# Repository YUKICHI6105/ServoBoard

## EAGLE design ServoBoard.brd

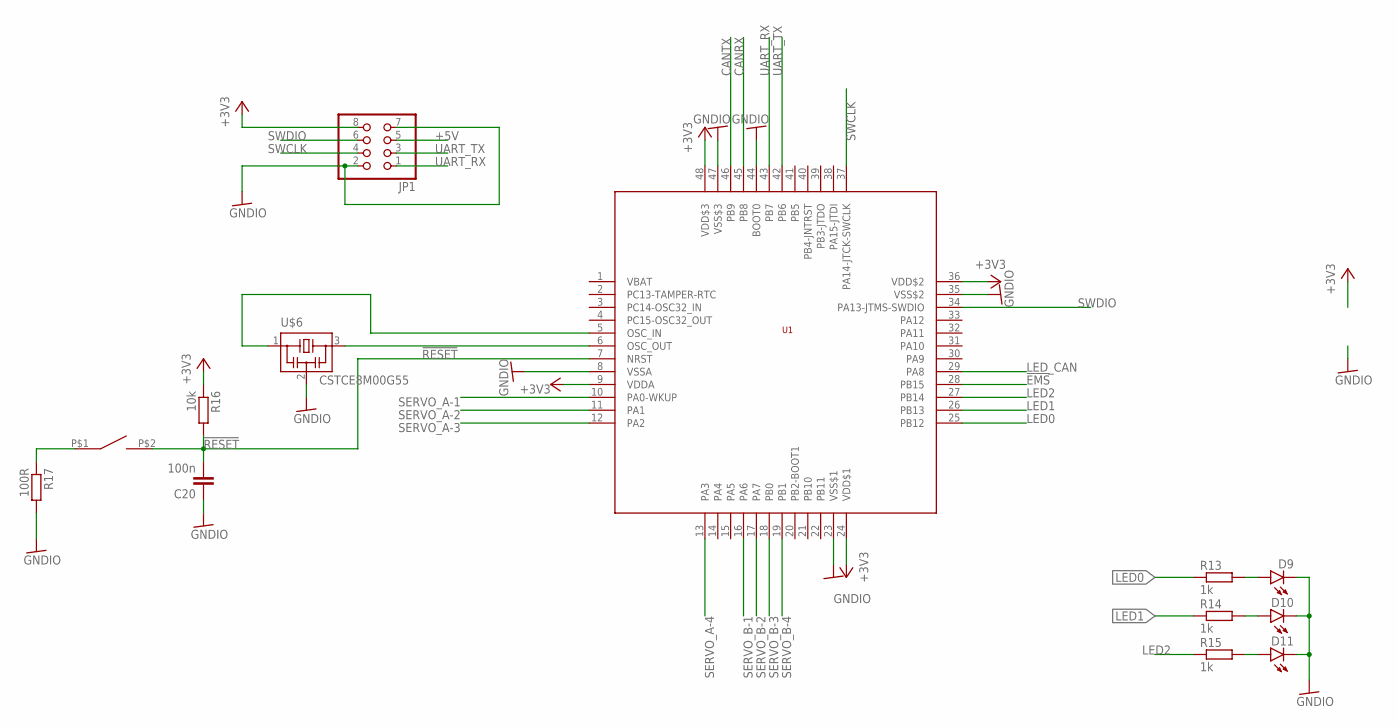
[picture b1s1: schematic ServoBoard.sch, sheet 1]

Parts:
C20: 100n; C0603
D9, D10, D11: LEDCHIPLED_0805; CHIPLED_0805
JP1: PINHD-2X4; 2X04
R13, R14, R15: 1k; R0603
R16: 10k; R0603
R17: 100R; R0603
SW1: SWITCH_TACTILETOP; SWITCH_TACTILE_3X6
U1: STM32F103C8; LQFP48
U$6: CSTCE8M00G55

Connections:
!EMS: U1.28 (PB15); also elsewhere on the board
!RESET: C20.2, R16.2, SW1.P$2 (2), U1.7 (NRST)
+3V3: JP1.8, R16.1, U1.9 (VDDA), U1.24 (VDD$1), U1.36 (VDD$2), U1.48 (VDD$3); also elsewhere on the board
+5V: JP1.5; also elsewhere on the board
CANRX: U1.45 (PB8); also elsewhere on the board
CANTX: U1.46 (PB9); also elsewhere on the board
GNDIO: C20.1, D9.C, D10.C, D11.C, JP1.2, JP1.7, R17.2, U1.8 (VSSA), U1.23 (VSS$1), U1.35 (VSS$2), U1.44 (BOOT0), U1.47 (VSS$3), U$6.2; also elsewhere on the board
LED0: R13.1, U1.25 (PB12)
LED1: R14.1, U1.26 (PB13)
LED2: R15.1, U1.27 (PB14)
LED_CAN: U1.29 (PA8); also elsewhere on the board
unnamed: D10.A, R14.2
unnamed: D9.A, R13.2
unnamed: U1.6 (OSC_OUT), U$6.3
unnamed: R17.1, SW1.P$1 (1)
unnamed: U1.5 (OSC_IN), U$6.1
unnamed: D11.A, R15.2
SERVO_A-1: U1.10 (PA0-WKUP); also elsewhere on the board
SERVO_A-2: U1.11 (PA1); also elsewhere on the board
SERVO_A-3: U1.12 (PA2); also elsewhere on the board
SERVO_A-4: U1.13 (PA3); also elsewhere on the board
SERVO_B-1: U1.16 (PA6); also elsewhere on the board
SERVO_B-2: U1.17 (PA7); also elsewhere on the board
SERVO_B-3: U1.18 (PB0); also elsewhere on the board
SERVO_B-4: U1.19 (PB1); also elsewhere on the board
SWCLK: JP1.4, U1.37 (PA14-JTCK-SWCLK)
SWDIO: JP1.6, U1.34 (PA13-JTMS-SWDIO)
UART_RX: JP1.1, U1.43 (PB7)
UART_TX: JP1.3, U1.42 (PB6)

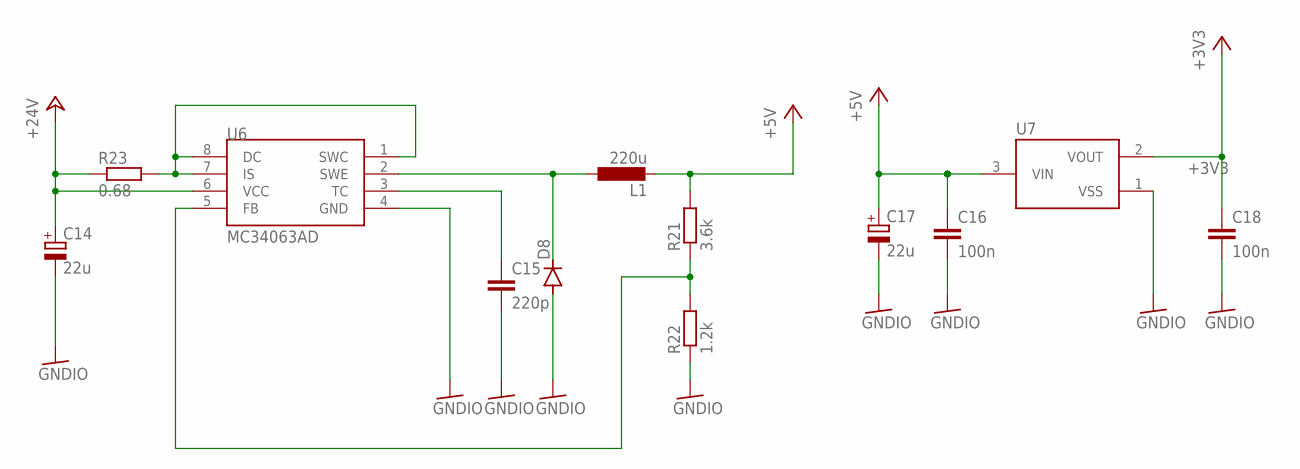
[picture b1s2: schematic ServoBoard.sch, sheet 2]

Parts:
C14, C17: 22u; E2-5
C15: 220p; C0603
C16, C18: 100n; C0603
D8: DIODE-SOD123; SOD123
L1: 220u; L5852
R21: 3.6k; R0603
R22: 1.2k; R0603
R23: 0.68; R1206
U6: MC34063AD; SOIC8
U7: XC6206; SOT95P240X110-3

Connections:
+3V3: C18.1, U7.2 (VOUT); also elsewhere on the board
+5V: C16.1, C17.+, L1.P$2 (2), R21.2, U7.3 (VIN); also elsewhere on the board
+24V: C14.+, R23.1, U6.6 (VCC); also elsewhere on the board
GNDIO: C14.-, C15.2, C16.2, C17.-, C18.2, D8.A, R22.1, U6.4 (GND), U7.1 (VSS); also elsewhere on the board
unnamed: R23.2, U6.1 (SWC), U6.7 (IS), U6.8 (DC)
unnamed: D8.C, L1.P$1 (1), U6.2 (SWE)
unnamed: C15.1, U6.3 (TC)
unnamed: R21.1, R22.2, U6.5 (FB)

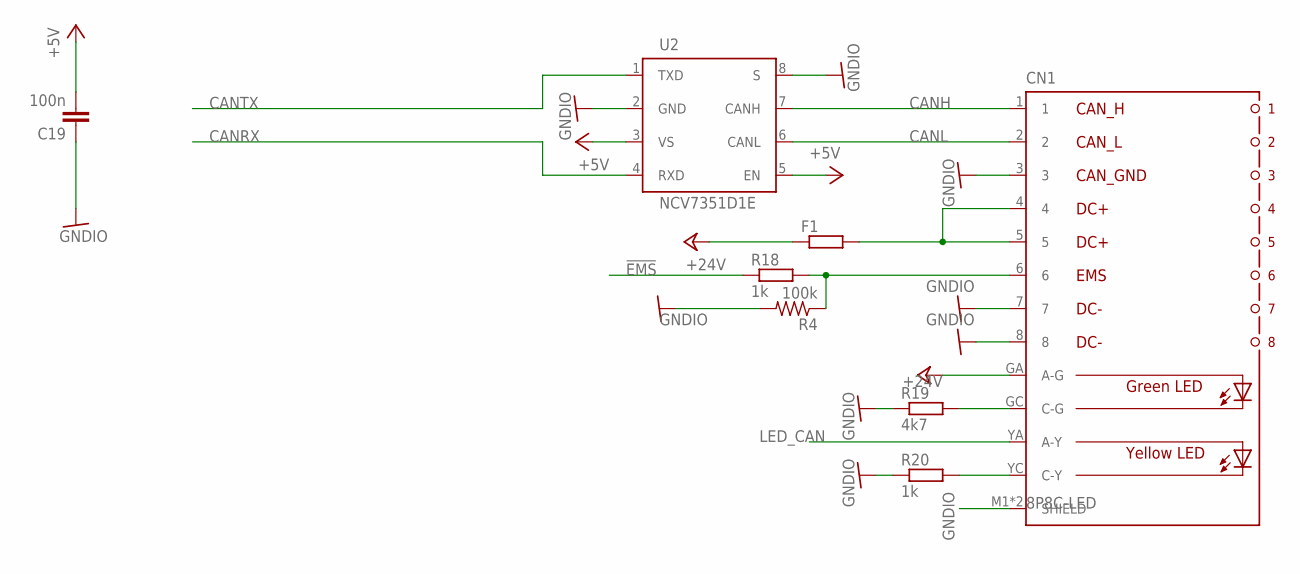
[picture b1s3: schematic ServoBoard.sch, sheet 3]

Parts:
C19: 100n; C0603
CN1: 8P8C-LED
F1: R-EU_R1206; R1206
R4: 100k; R0603
R18, R20: 1k; R0603
R19: 4k7; R0603
U2: NCV7351D1E; SO08

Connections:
!EMS: R18.1; also elsewhere on the board
+5V: C19.2, U2.3 (VS), U2.5 (EN); also elsewhere on the board
+24V: CN1.GA (A-G), F1.1; also elsewhere on the board
CANH: CN1.1, U2.7 (CANH)
CANL: CN1.2, U2.6 (CANL)
CANRX: U2.4 (RXD); also elsewhere on the board
CANTX: U2.1 (TXD); also elsewhere on the board
GNDIO: C19.1, CN1.3, CN1.7, CN1.8, CN1.M1 (SHIELD), CN1.M2 (SHIELD), R4.2, R19.1, R20.1, U2.2 (GND), U2.8 (S); also elsewhere on the board
LED_CAN: CN1.YA (A-Y); also elsewhere on the board
unnamed: CN1.4, CN1.5, F1.2
unnamed: CN1.YC (C-Y), R20.2
unnamed: CN1.GC (C-G), R19.2
unnamed: CN1.6, R4.1, R18.2

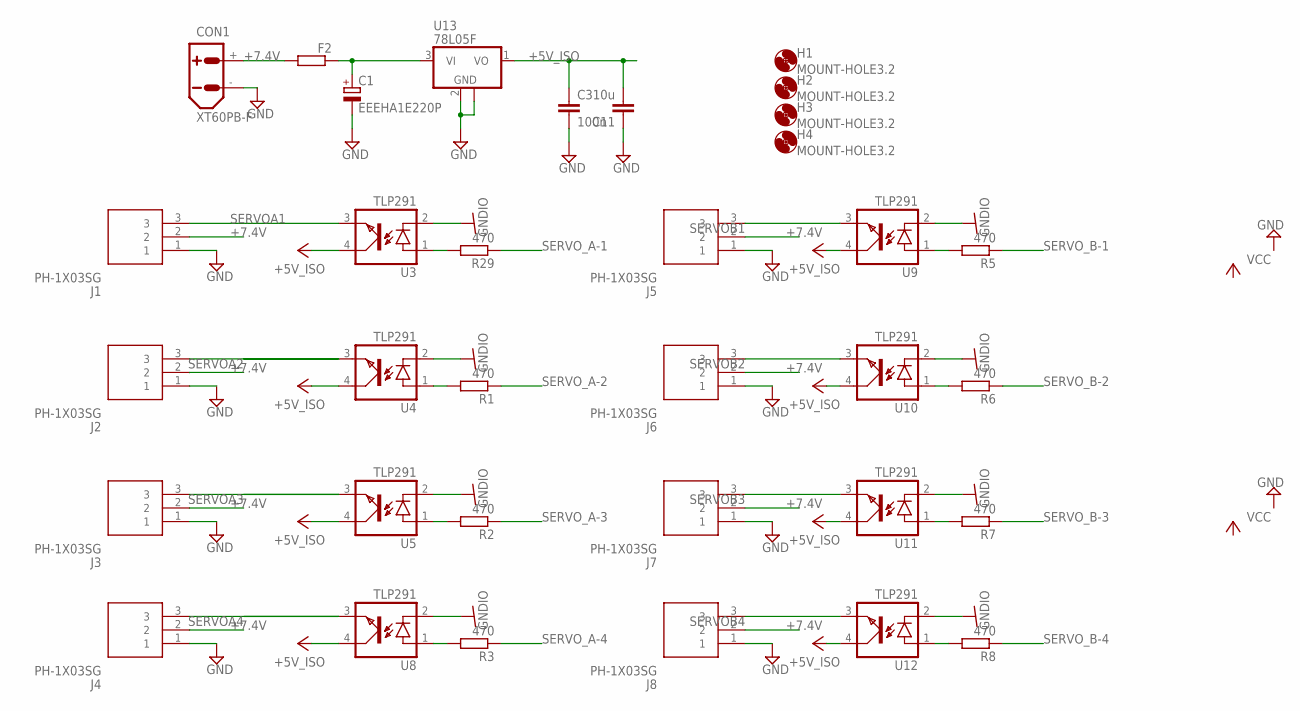
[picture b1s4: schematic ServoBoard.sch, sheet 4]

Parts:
C1: EEEHA1E220P; 153CLV-0605
C3: 100n; C0603
C11: 10u; C1210
CON1: XT60PB-F
F2: R-EU_R1206; R1206
H1, H2, H3, H4: MOUNT-HOLE3.2; 3,2
J1, J2, J3, J4, J5, J6, J7, J8: PH-1X03SG; HDRV3W66P254_1X3_762X250X895P
R1, R2, R3, R5, R6, R7, R8, R29: 470; R0603
U3, U4, U5, U8, U9, U10, U11, U12: TLP291; MINI-FLAT-4
U13: 78L05F; SOT89

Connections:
+5V_ISO: C3.1, C11.2, U3.4 (COL), U4.4 (COL), U5.4 (COL), U8.4 (COL), U9.4 (COL), U10.4 (COL), U11.4 (COL), U12.4 (COL), U13.1 (VO)
+7.4V: CON1.+, F2.2, J1.2, J2.2, J3.2, J4.2, J5.2, J6.2, J7.2, J8.2
GND: C1.-, C3.2, C11.1, CON1.-, J1.1, J2.1, J3.1, J4.1, J5.1, J6.1, J7.1, J8.1, U13.2 (GND), U13.2@1 (GND)
GNDIO: U3.2 (C), U4.2 (C), U5.2 (C), U8.2 (C), U9.2 (C), U10.2 (C), U11.2 (C), U12.2 (C); also elsewhere on the board
unnamed: R3.2, U8.1 (A)
unnamed: R5.2, U9.1 (A)
unnamed: R1.2, U4.1 (A)
unnamed: C1.+, F2.1, U13.3 (VI)
unnamed: R6.2, U10.1 (A)
unnamed: R2.2, U5.1 (A)
unnamed: R7.2, U11.1 (A)
unnamed: R29.2, U3.1 (A)
unnamed: R8.2, U12.1 (A)
SERVOA1: J1.3, U3.3 (EMIT)
SERVOA2: J2.3, U4.3 (EMIT)
SERVOA3: J3.3, U5.3 (EMIT)
SERVOA4: J4.3, U8.3 (EMIT)
SERVOB1: J5.3, U9.3 (EMIT)
SERVOB2: J6.3, U10.3 (EMIT)
SERVOB3: J7.3, U11.3 (EMIT)
SERVOB4: J8.3, U12.3 (EMIT)
SERVO_A-1: R29.1; also elsewhere on the board
SERVO_A-2: R1.1; also elsewhere on the board
SERVO_A-3: R2.1; also elsewhere on the board
SERVO_A-4: R3.1; also elsewhere on the board
SERVO_B-1: R5.1; also elsewhere on the board
SERVO_B-2: R6.1; also elsewhere on the board
SERVO_B-3: R7.1; also elsewhere on the board
SERVO_B-4: R8.1; also elsewhere on the board

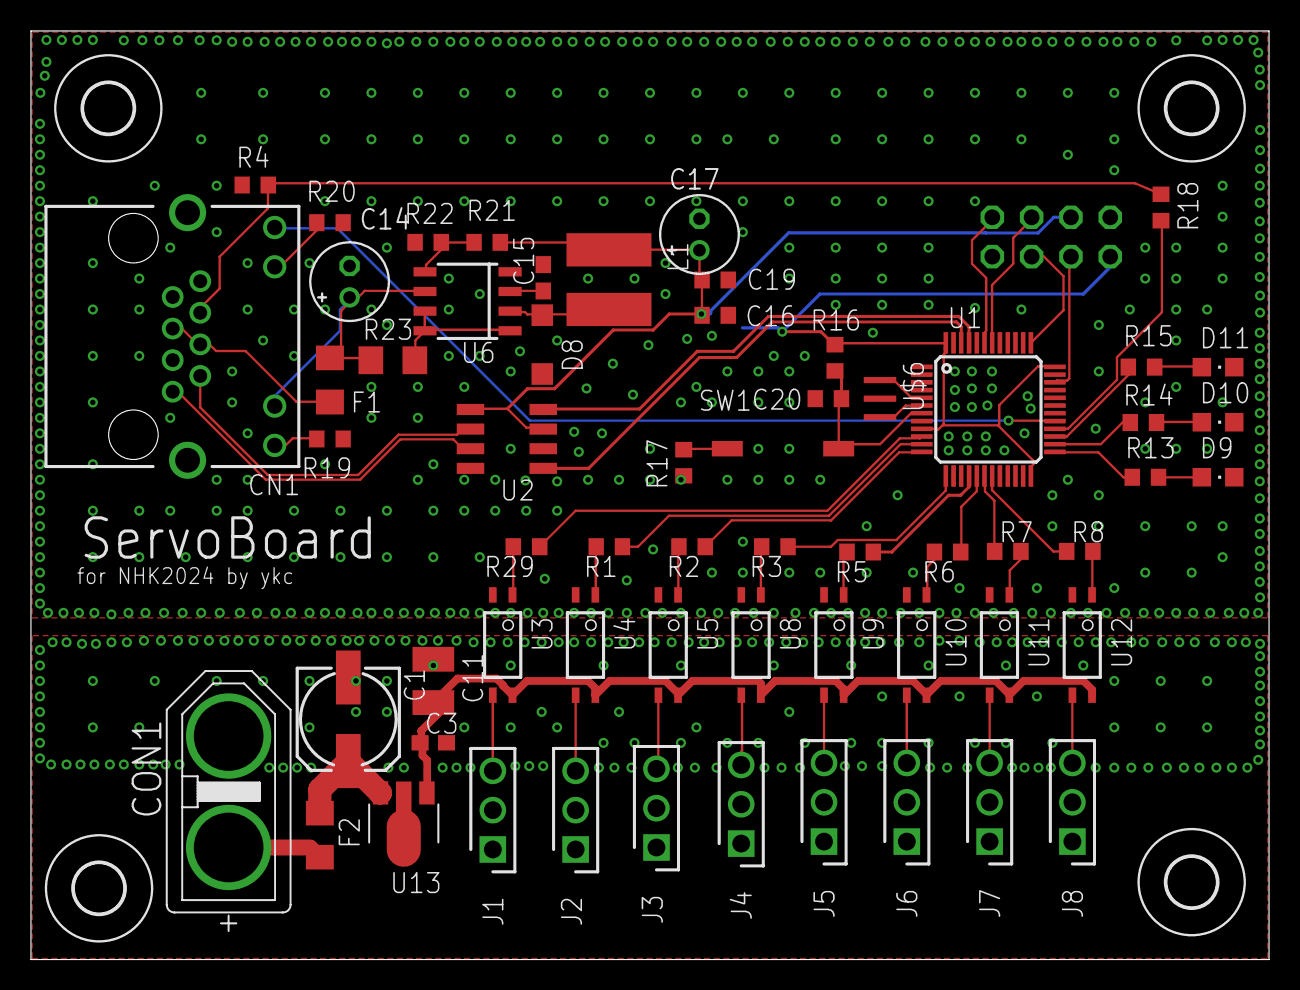
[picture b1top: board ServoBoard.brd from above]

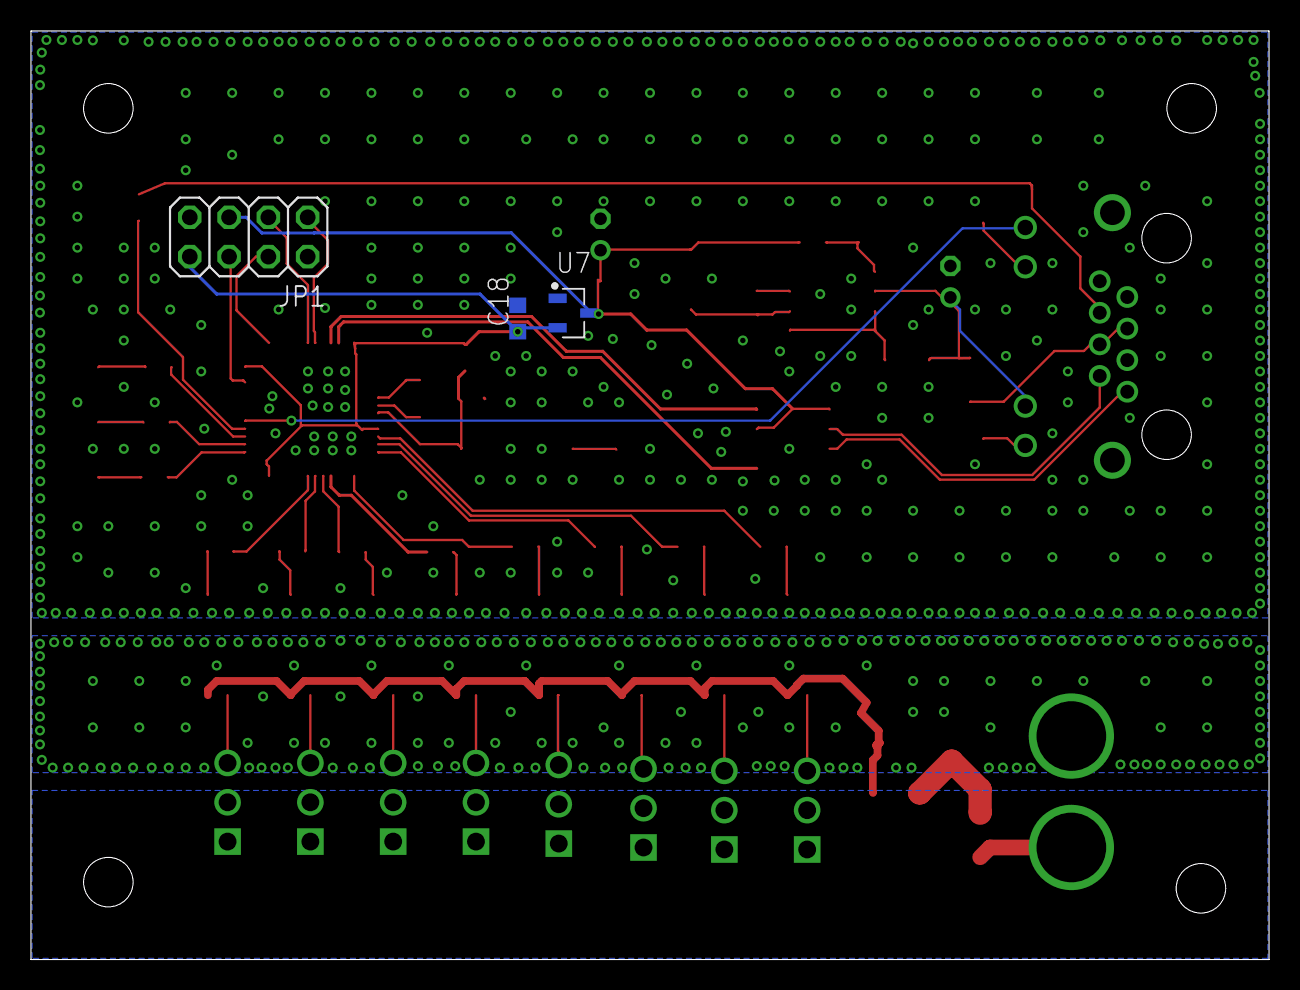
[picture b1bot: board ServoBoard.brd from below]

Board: 2 copper layers, 80.0 x 60.0 mm, 67 parts (3 on the bottom side), 60 nets.
